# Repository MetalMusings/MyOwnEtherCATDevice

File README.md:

# MetalMusings EtherCAT device

This repository contains the EtherCAT devices I have designed, built and put in use in linuxcnc.

Everything should be here: 
- Schematics, PCB layouts, and what is needed to build the boards.
- Software tools to create an ESI-file and program the ESC eeprom. 
- Software tools to create the application running on a STM32F407VG.
- A big learning curve is hidden in here as well

I have (so far) used two different ESC ICs: LAN9252 and Ax58100. 
Both work, I can't really see a difference. 
The Ax58100 has a leg spacing of 0.4 mm, 0.5 mm for the LAN9252, if that matters.
On paper the Ax58100 has more builtin functionality like stepper motor drivers,
but the documentation is lacking. Or my understanding of the documentation is lacking.
The Ax58100 supposedly has more efficient access to registers and data.
The indirection scheme is the main objection to using LAN9252, I have read.
The LAN9252 is the true and tested IC of the two. If you don't know, go for the LAN9252.

The EtherCAT cards, which I call EaserCAT cards, use an EtherCAT chip and a normal MCU.
I have used the STM32F407VGT6. The EaserCAT chip does the network talk and other 
EtherCAT things. The STM32 does the application things, like reading and setting pins high or low,
reading encoder inputs, generate stepper motor pulses and other interesting applications one can think of.
There is a narrow interface between the two: SPI and a couple of lines for synchronization.
Any decent MCU can do that, it doesn't have to be a STM32F407VGT6. I have tested with a esp32 with success.
Feel free to experiment with other processors.

I learned most of what I know about EtherCAT through a number of Youtube videos I made.
There are accompanying git branches. For example, for video 8 you can check out the
Video8 branch to get the software tree in the state at the video.
More info on the videos, which are now more of historical interest, but also a bit of learning by following [this link](Videos.md)

And of course, this work builds on the work of many others. This would not be possible without their work. 
I'm just reusing what they did and maybe expanding on it.

Here is the start of [building instructions](Build.md)

## EaserCAT 2000 - a testbench for ESC+MCU, SOES, stepper generator, linuxcnc

This was the first card that got used in Linuxcnc. Follow [link here](Cards/EaserCAT-2000/)
I think I got it working pretty well in the end. There was, and still is, an issue with
synchronization between the linuxcnc servo-loop and the ESC DC loop.
I don't remember the status of it anymore, it was some time ago I worked with it.
The main thing was that it lacked optocouplers and isolation for the external signals.

## EaserCAT 3000 - All in one board with Ax58100

This card is an evolution of the EaserCAT 2000 and was intended to be used in my plasma cutter.
It features four stepper driver outputs, input for a THCAD arc voltage card, an encoder, 
an analog output (for spindle +- 10V), eight digital inputs, four digital outputs, 
plus some 12 I/O for any possible extension. The IOs are isolated from the MCU.

However, I couldn't get this card to work, almost at all. The Ax58100 didn't even load the eeprom. 
Struggling with the documentation for the Ax58100, which formed my negative opinion about that,
I gave up and let it sit for over half a year. It was first when someone came and asked 
questions around it I had another look. I built a new board, and it all started to work.
At time of writing it all seems to work.

The latest vesion of the firmware has all parameters for step generators as PDOs.

[Link here](Cards/EaserCAT-3000-Digital-Stepper-Analog-Encoder-Frequency/)

## EaserCAT 4000 - THCAD reader

Faced with the problems with the EaserCAT 3000 board, and still wanting to use EtherCAT 
in my upcoming plasma cutter, I made this board whos single purpose is to read 
the PWM frequency from Mesa's THCAD board.\
The THCAD board reads the voltage between 
the plasma torch and the workpiece which is around 100V. Highly isolated, and with 
a voltage to frequency converter it delivers a differential pwm signal. 
The frequency of this signal can be related to the voltage.\
That's what is needed for linuxcnc torch height control.

In the tests on the bench this can read at least up to 200 kHz, but its's better to be below 100 kHz.
The THCAD has a frequency divider one can set to make the frequency range nicely match this.
It seems to work fine so far. 
Implementation is with interrupts. \
A better option would have been to use TIM2's PWM_INPUT function, which can work with several MHz frequency. 
I tried the PWM_INPUT method a lot but couldn't get it to work. The current method still works, though.
If time and interests are in phase with the moon, I might look at PWM_INPUT again.

This board is now relegated to history, replaced by the EaserCAT-6000.

[Link here](Cards/EaserCAT-4000-THCAD-Reader/)

## EaserCAT 5000 - Digital IO without MCU

A card just doing Digital Input and Digital Output. The intentions were to read 
limit switches and some other switches around the plasma torch. And to switch on the plasma torch.
It's a single LAN9252, configured for local IO. Optocouplers are attached to IO pins for isolation.
It has been tested on the bench, it works with TwinCAT.

HOWEVER, it doesn't work, and will not work, with linuxcnc. As I've learned,
the IgH EtherCAT master needs a CoE client (CANopen over EtherCAT).
The LAN9252 in DIO mode is only an EtherCAT client and can't be turned
into a CoE client. And the IgH EtherCAT application interface for real-time
communication can not be downgraded to work with a pure EtherCAT client,
it requires a CoE client.

To add CoE functionality means to add number of objects at certain positions
in the client and that can not be done to the LAN9252. It is what it is.
In a setup with LAN9252 with MCU, those objects are created in the firmware,
so there it works.

This board is now relegated to history, replaced by the EaserCAT-6000.

## EaserCAT 6000 - Digital IO and frequency input

Finally, a card that's actually used in a real system. This card is used in my plasma cutter. 
It has 12 digital inputs, 4 digital outputs and a frequency counter to get
the input from Mesa's THCAD (reader of voltage between plasma nozzle and workpiece).\
All digital IOs are opto-isolated and the frequency input uses a RS-485 receiver.

In the plasma cutter, it does the job. There are three ECT60 stepper motor drivers.
And the EaserCAT-6000 card. It handles limit switches for X, Y and Z, floating switch,
break-away switch, and plasma Arc OK signal. There is room for e-stop and other switches.\
The plasma torch is switched on using one of the digital outputs.\
THCAD is an older model with full voltage input. Frequency divider is set to 1/32.

This board replaces EaserCAT-4000 and EaserCAT-5000. 

[Link here](Cards/EaserCAT-6000-THCAD-reader+Digital-IO/)

A few weeks later and I've used this card in the plasma cutter for quite a bit of cutting and it hasn't missed a beat. Works so well. THC follows the sheet surface up and down. Awesome.

## EaserCAT Torch Height Control - EaserCAT 7000 with THTIC and THTIC2

Actually something useful again - not one, but two, plasma torch voltage readers.
They replace the THCAD board and comes with the entire chain from voltage reading to the introduction of a calibrated voltage to linuxcnc for use in QtPlasmaC. 

Let's start with the plasma cutter. There is either a THTIC or THTIC2 mini-board, which reads the plasma torch voltage, and through a voltage divider lowers it to about 2 Volts during cutting. This voltage is converted by an analog to digital converter and feeds the digitized voltage to the EaserCAT 7000 board via an I2C bus (cable). The EaserCAT 7000 board makes the voltage available both as the raw read voltage for further scaling, or as a calibrated voltage using entered calibration constants.

The plasma torch voltage is DCEN - DC Electrode Negative. The workpiece ground is often connected to ground/earth.
With ground as the reference voltage, the plasma torch voltage ranges between 0 V and -200 V.
An inverting operational amplifier switches the polarity for the ADC. The ground planes on the circuit board are connected to the workpiece ground.

An important feature of THCTIC and THCTIC2 is that the plasma voltage side is isolated from the linuxcnc signal side. The isolation level is better than 1.5 kV. This is achieved by an I2C isolator and an isolated DC-DC converter. The difference between the two cards is the choice of ADC. THTIC uses MCP3221 and THTIC2 uses ADS1014. Both are 12-bit analog to digital converters, ADS1014 is perhaps an 11-bit, both with sampling rates around 3 kHz. A newly measured voltage value can be obtained every 1 ms. Of course you only choose one of the two. Since it seemed pretty easy when I did it, I made two different ones. Always good to have options.

The boards are relatively small, 42x30 mm. Voltage 5V in, current less than 10 mA. I2C Data and clock. 

### THTIC

### THTIC2

### EaserCAT-7000 Digital IO and I2C voltage reader

EaserCAT-7000 is an EaserCAT-6000 board where the THCAD frequency input has been replaced by the I2C bus.
There are twelve digital inputs and four digital outputs.

Currently the EaserCAT-7000 can handle two I2C voltage readers, on different I2C addresses.\
Configuration of the connected I2C devices is done by setting the voltage reader type in SDOs 0x2000:1 and 0x2001:1 for device 1 and 2. The I2C device type is set to 0 by default. A zero means no I2C ADC. Entering a 1 in 0x2000:0 selects the MCP3221, and a 2 in 0x2000:0 selects the ADS1014.\
The I2C address for the ADC is written into SDOs 0x2000:2 and 0x2001:2. The address for the MCP3221 is selected when it is purchased - there are 8 different models each with a different I2C address 0x48-0x4f. The THTIC2 board has the address fixed at 0x48; can be modified during pcb assembly to 0x49 quite easily - check datasheet. Short version is to cut Addr-Gnd and add Addr-Vcc.

Pay attention to the polarity when connecting the plasma voltage leads the THTIC and THTIC2. Varc+ must have higher voltage potential the Varc- (as one would expect). The voltage divisor may need to be adjusted, there is now one 100 kOhm resistor and a 2.2 kOhm resistor, which brings down 100 V to around 2 V. Adjust as needed. For high voltage, pay attention to the max allowed voltage of the resistor. The ADC likes to have around 2-3 Volts when cutting.

The experience with these cards has been very good. I used the THTIC a lot, cutting for at least an hour of cutting time, with THC enabled and active. A status variable shows that it has been working the whole time, no stops or resets. After that I switched to the THTIC2 card and have been using that since. Works really well.

## THCLIP Enable ohmic sensing with the IPTM-60 torch

This is for the torches known as IPT-60 PT-60 S45 IPTM-60 IPTM-80 and many more that have blowback start with the torch tip exposed and normally shortened to the torch electrode. Normally this torch can't use ohmic sensing since all parts are connected to ground. At least on my machine, a Herocut 8000, the blowback start cable from the torch can be cut during sensing. This enables ohmic sensing and it continues to operate in other situations.

I tried at first to use the normal Arc voltage reader to detect any contact between the torch and the work piece during probing. However, that was not reliable - it seems there is electronics involved with the arc voltage. Don't want to know details. 

I put a second voltage reader THTIC2 close to the THCLIP and measure the 24V applied after the relay. Monitoring this voltage turns out to be reliable and makes the ohmic sensing work really well.

I have made an adaptation to the EaserCAT 7000 to handle the contact. The relay has a short, some 10 msecs, setup time. The read voltage must therefor first go above the voltage limit before it starts to scan for the voltage to go below the voltage limit which indicates contact.

The Trafimet torch hose connectors are called FY0022 and FY0023. The relay is a 24V 40A standard car relay. Check out the Kicad schematics for the other parts.

Leads 1 and 4 are the blowback arc start ground leads in my torch. They get cut by the relay during ohmic sensing. Voltage is measured on connector J3, between pin 1 and pin 2.

## License

Don't violate the original licenses. No warranties. Use it any way you like.\
Remember: It is a hobby project, not a product.

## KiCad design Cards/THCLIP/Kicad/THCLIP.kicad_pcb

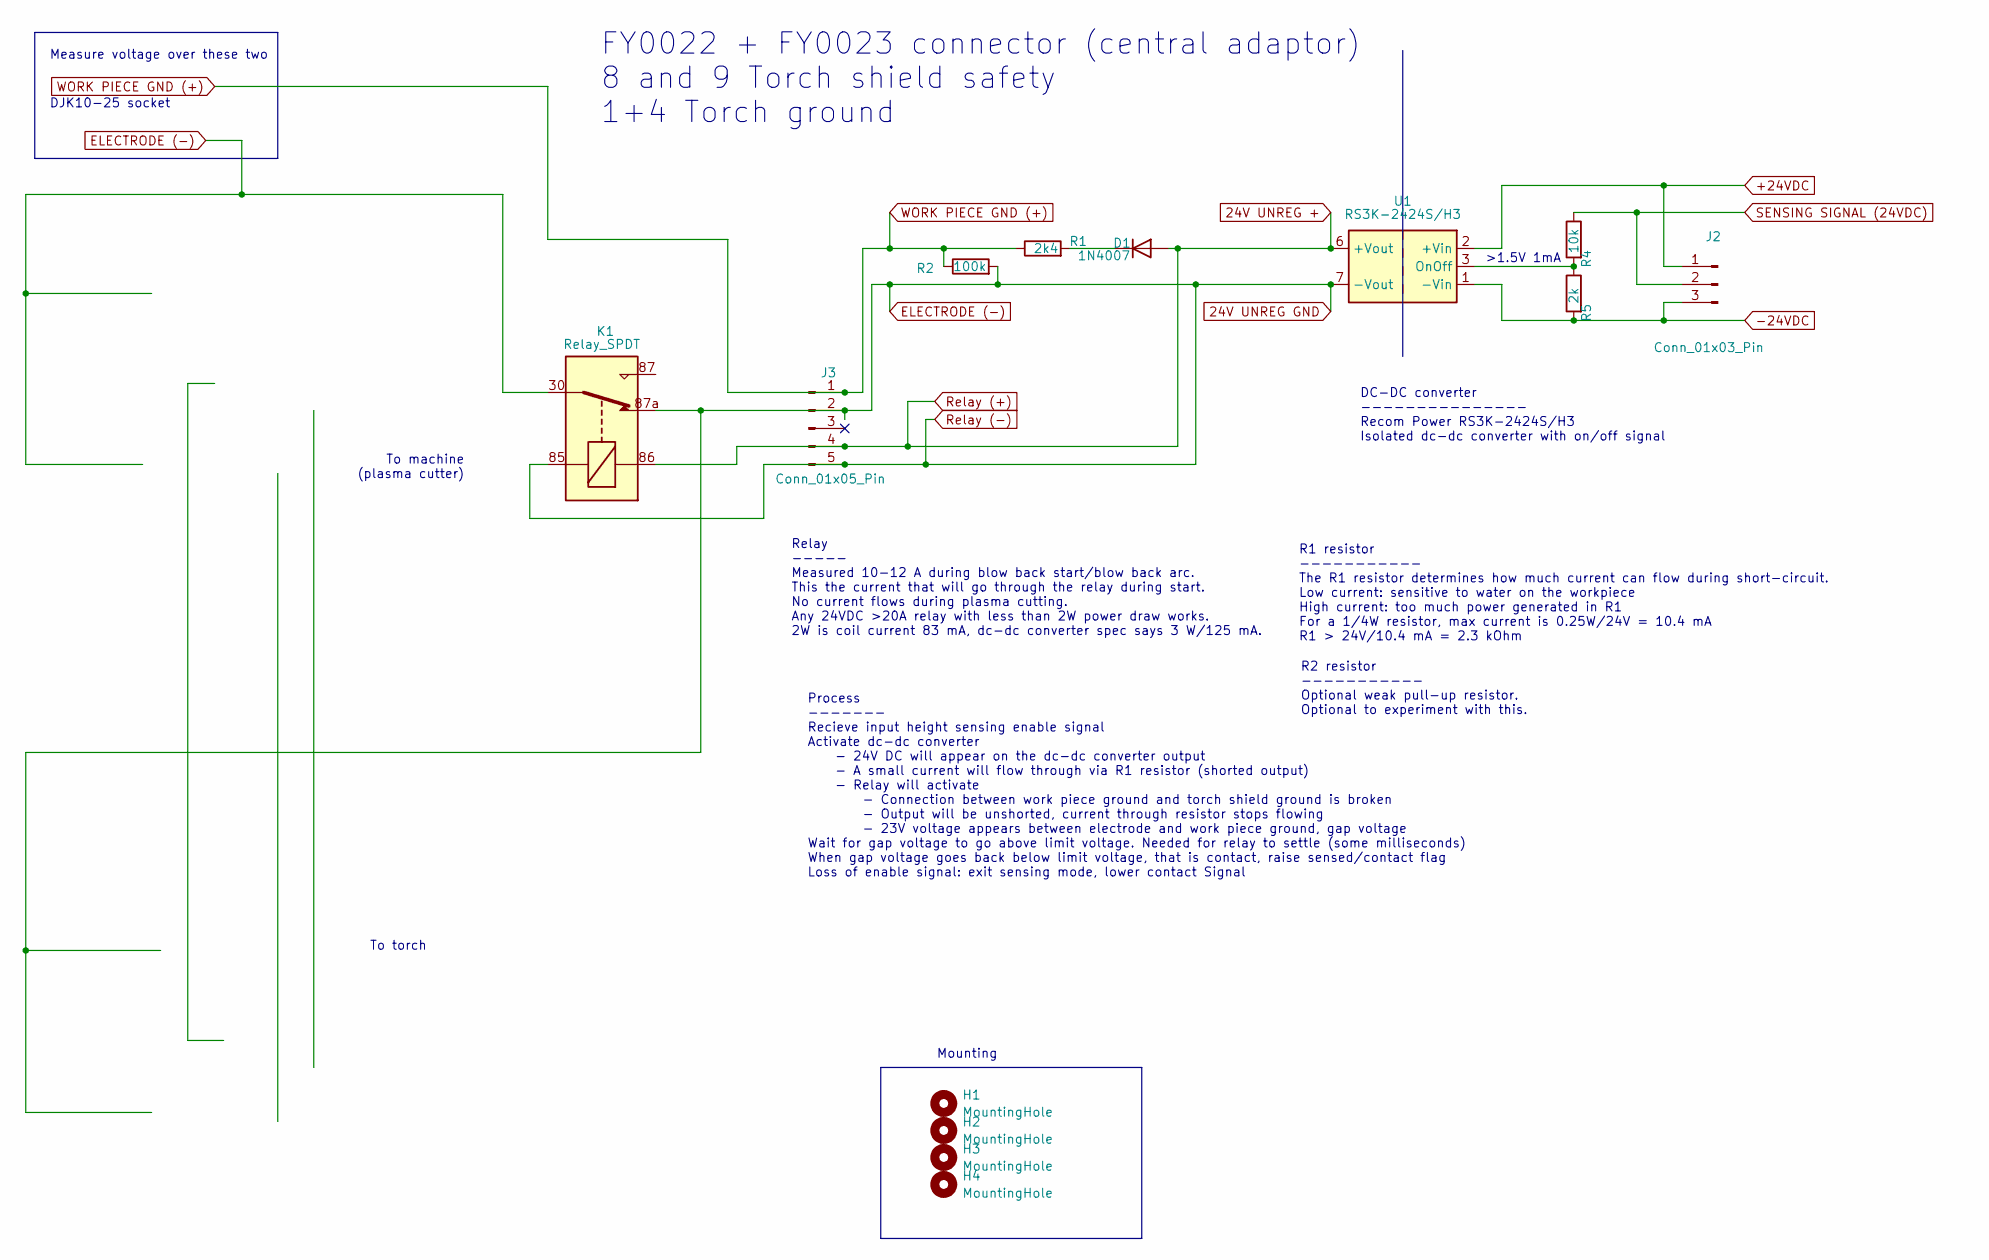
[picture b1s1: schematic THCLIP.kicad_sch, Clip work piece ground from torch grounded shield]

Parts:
D1: 1N4007; D_DO-41_SOD81_P10.16mm_Horizontal
H1, H2, H3, H4: MountingHole; MountingHole_3.2mm_M3
J2: Conn_01x03_Pin; PhoenixContact_MCV_1,5_3-G-3.5_1x03_P3.50mm_Vertical
J3: Conn_01x05_Pin; PhoenixContact_MCV_1,5_5-G-3.5_1x05_P3.50mm_Vertical
K1: Relay_SPDT
R1: 2k4; R_Axial_DIN0207_L6.3mm_D2.5mm_P10.16mm_Horizontal
R2: 100k; R_Axial_DIN0207_L6.3mm_D2.5mm_P10.16mm_Horizontal
R4: 10k; R_0805_2012Metric_Pad1.20x1.40mm_HandSolder
R5: 2k; R_0805_2012Metric_Pad1.20x1.40mm_HandSolder
U1: RS3K-2424S/H3; Converter_DCDC_TRACO_TEC3-24xxUI_THT

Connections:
24V UNREG +: D1.2 (A), J3.4, K1.86, U1.6 (+Vout)
24V UNREG GND: J3.2, J3.5, K1.30, K1.85, K1.87a, R2.2, U1.7 (-Vout)
+24VDC: J2.1, U1.2 (+Vin)
-24VDC: J2.3, R5.2, U1.1 (-Vin)
unnamed: D1.1 (K), R1.2
unnamed: R4.2, R5.1, U1.3 (OnOff)
SENSING SIGNAL (24VDC): J2.2, R4.1
WORK PIECE GND (+): J3.1, R1.1, R2.1

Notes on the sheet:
DJK10-25 socket
Process ------- Recieve input height sensing enable signal Activate dc-dc converter - 24V DC will appear on the dc-dc converter output - A small current will flow through via R1 resistor (shorted output) - Relay will activate - Connection between work piece ground and torch shield ground is broken 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
>1.5V 1mA
To torch
Mounting
To machine (plasma cutter)
FY0022 + FY0023 connector (central adaptor) 8 and 9 Torch shield safety 1+4 Torch ground
Measure voltage over these two
R1 resistor ----------- The R1 resistor determines how much current can flow during short-circuit. Low current: sensitive to water on the workpiece High current: too much power generated in R1 For a 1/4W resistor, max current is 0.25W/24V = 10.4 mA R1 > 24V/10.4 mA = 2.3 kOhm
DC-DC converter --------------- Recom Power RS3K-2424S/H3 Isolated dc-dc converter with on/off signal
R2 resistor ----------- Optional weak pull-up resistor. Optional to experiment with this.
Relay ----- Measured 10-12 A during blow back start/blow back arc. This the current that will go through the relay during start. No current flows during plasma cutting. Any 24VDC >20A relay with less than 2W power draw works. 2W is coil current 83 mA, dc-dc converter spec says 3 W/125 mA.

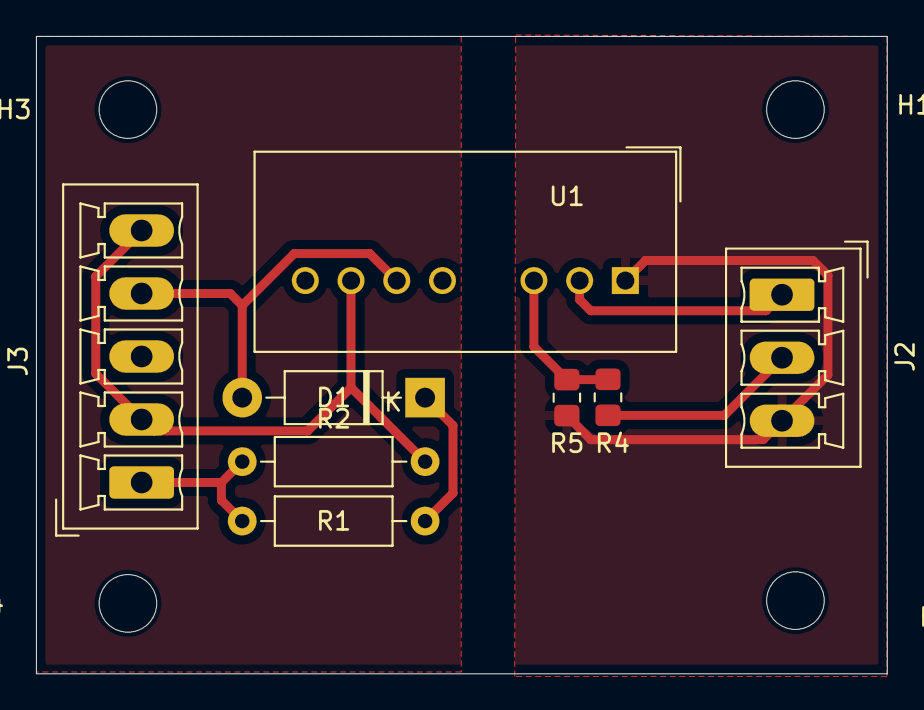
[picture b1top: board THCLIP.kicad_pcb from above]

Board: 2 copper layers, 47.3 x 35.4 mm, 12 parts (0 on the bottom side), 8 nets.

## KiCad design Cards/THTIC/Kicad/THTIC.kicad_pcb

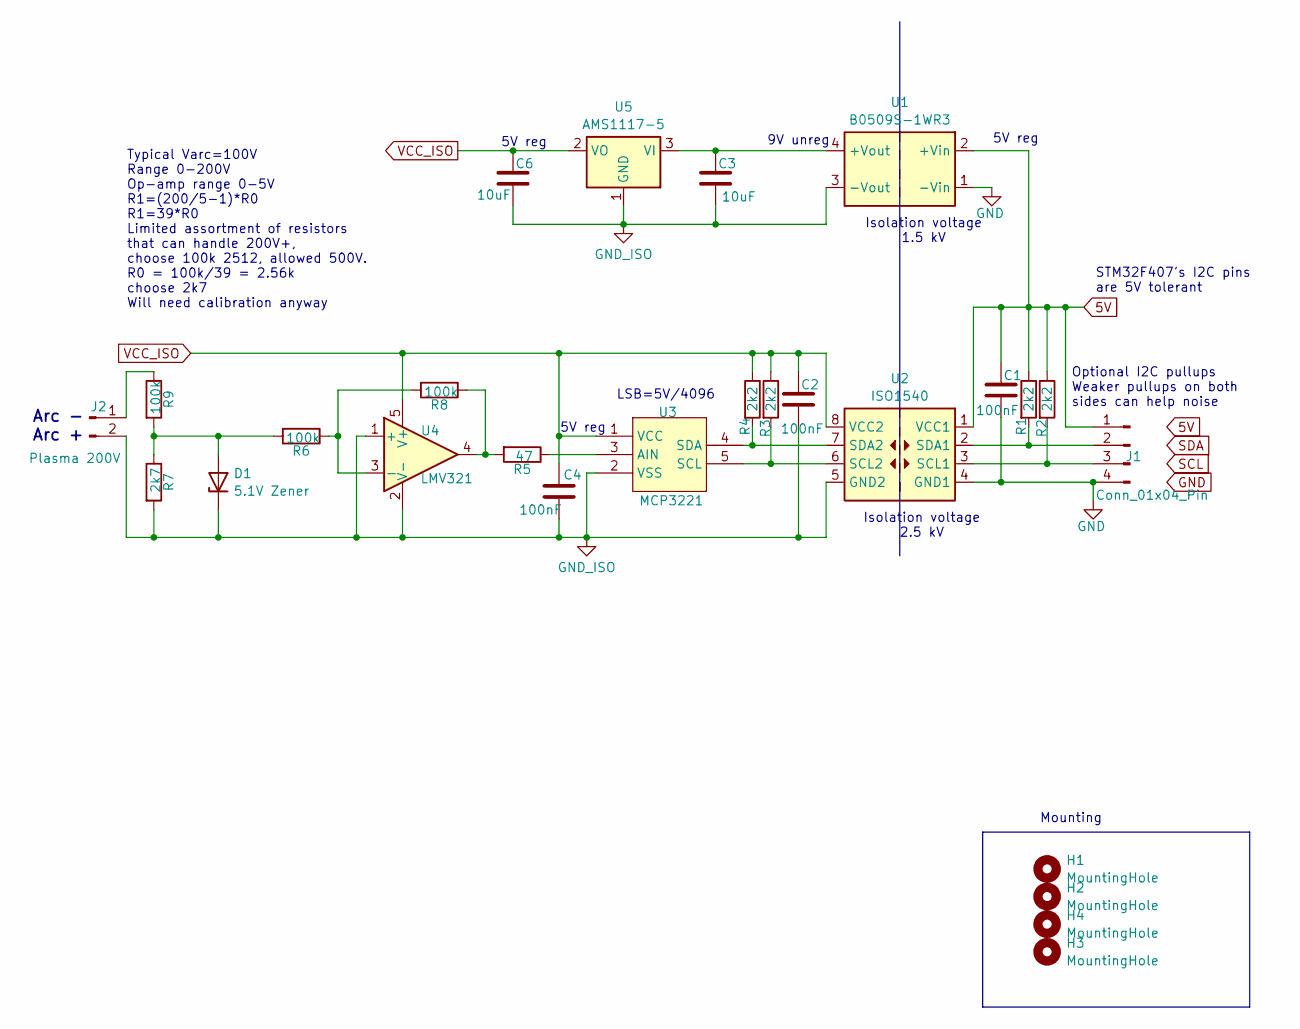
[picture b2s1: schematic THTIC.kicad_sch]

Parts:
C1, C2, C4: 100nF; C_0805_2012Metric
C3, C6: 10uF; C_0805_2012Metric
D1: 5.1V Zener; D_SOD-323_HandSoldering
H1, H2, H3, H4: MountingHole; MountingHole_3.2mm_M3
J1: Conn_01x04_Pin; PhoenixContact_MCV_1,5_4-G-3.5_1x04_P3.50mm_Vertical
J2: Plasma 200V; PhoenixContact_MCV_1,5_2-G-3.5_1x02_P3.50mm_Vertical
R1, R2, R3, R4: 2k2; R_0805_2012Metric
R5: 47; R_0805_2012Metric
R6, R8: 100k; R_0805_2012Metric
R7: 2k7; R_0805_2012Metric
R9: 100k; R_2512_6332Metric
U1: B0509S-1WR3; Converter_DCDC_TRACO_TEA1-xxxx_THT
U2: ISO1540; SOIC-8_3.9x4.9mm_P1.27mm
U3: MCP3221; SOT-23-5
U4: LMV321; SOT-23-5
U5: AMS1117-5; SOT-223-3_TabPin2

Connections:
5V: C1.1, J1.1, R1.1, R2.1, U1.2 (+Vin), U2.1 (VCC1)
GND: C1.2, J1.4, U1.1 (-Vin), U2.4 (GND1)
GND_ISO: C2.2, C3.2, C4.2, C6.2, D1.1 (K), J2.2, R7.2, U1.3 (-Vout), U2.5 (GND2), U3.2 (VSS), U4.1 (+), U4.2 (V-), U5.1 (GND); also elsewhere on the board
unnamed: D1.2 (A), R6.2, R7.1, R9.2
unnamed: J1.2, R1.2, U2.2 (SDA1)
unnamed: J1.3, R2.2, U2.3 (SCL1)
unnamed: J2.1, R9.1
unnamed: R5.2, R8.1, U4.4
unnamed: C3.1, U1.4 (+Vout), U5.3 (VI)
unnamed: R3.2, U2.6 (SCL2), U3.5 (SCL)
unnamed: R4.2, U2.7 (SDA2), U3.4 (SDA)
unnamed: R5.1, U3.3 (AIN)
unnamed: R6.1, R8.2, U4.3 (-)
VCC_ISO: C2.1, C4.1, C6.1, R3.1, R4.1, U2.8 (VCC2), U3.1 (VCC), U4.5 (V+), U5.2 (VO); also elsewhere on the board

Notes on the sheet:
Mounting
5V reg
Isolation voltage 2.5 kV
STM32F407's I2C pins are 5V tolerant
9V unreg
LSB=5V/4096
Optional I2C pullups Weaker pullups on both sides can help noise
Isolation voltage 1.5 kV
Typical Varc=100V Range 0-200V Op-amp range 0-5V R1=(200/5-1)*R0 R1=39*R0 Limited assortment of resistors that can handle 200V+, choose 100k 2512, allowed 500V. R0 = 100k/39 = 2.56k choose 2k7 Will need calibration anyway
Arc - Arc +

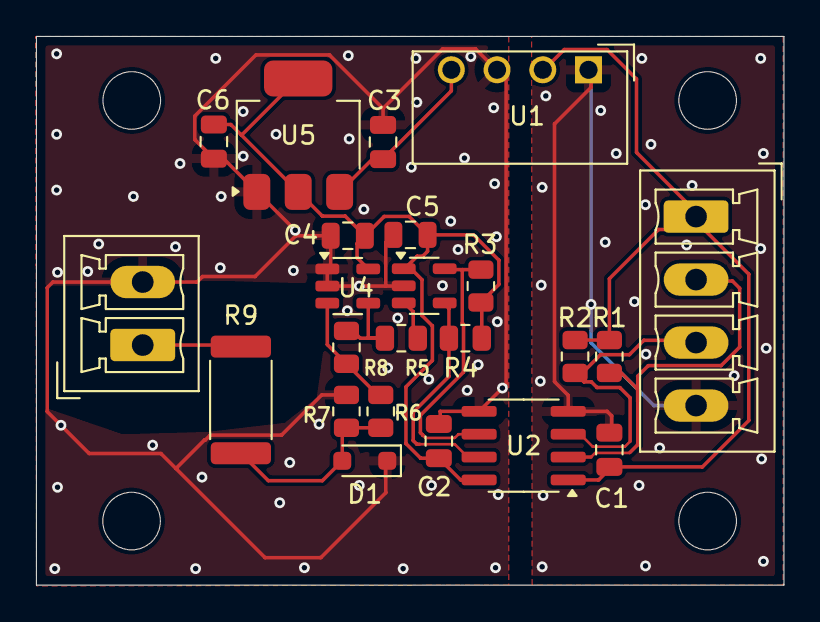
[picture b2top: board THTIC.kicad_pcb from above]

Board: 2 copper layers, 41.5 x 30.5 mm, 27 parts (0 on the bottom side), 14 nets.

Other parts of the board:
C5: 100nF; C_0805_2012Metric

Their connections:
GND_ISO: C5.2; also elsewhere on the board
VCC_ISO: C5.1; also elsewhere on the board

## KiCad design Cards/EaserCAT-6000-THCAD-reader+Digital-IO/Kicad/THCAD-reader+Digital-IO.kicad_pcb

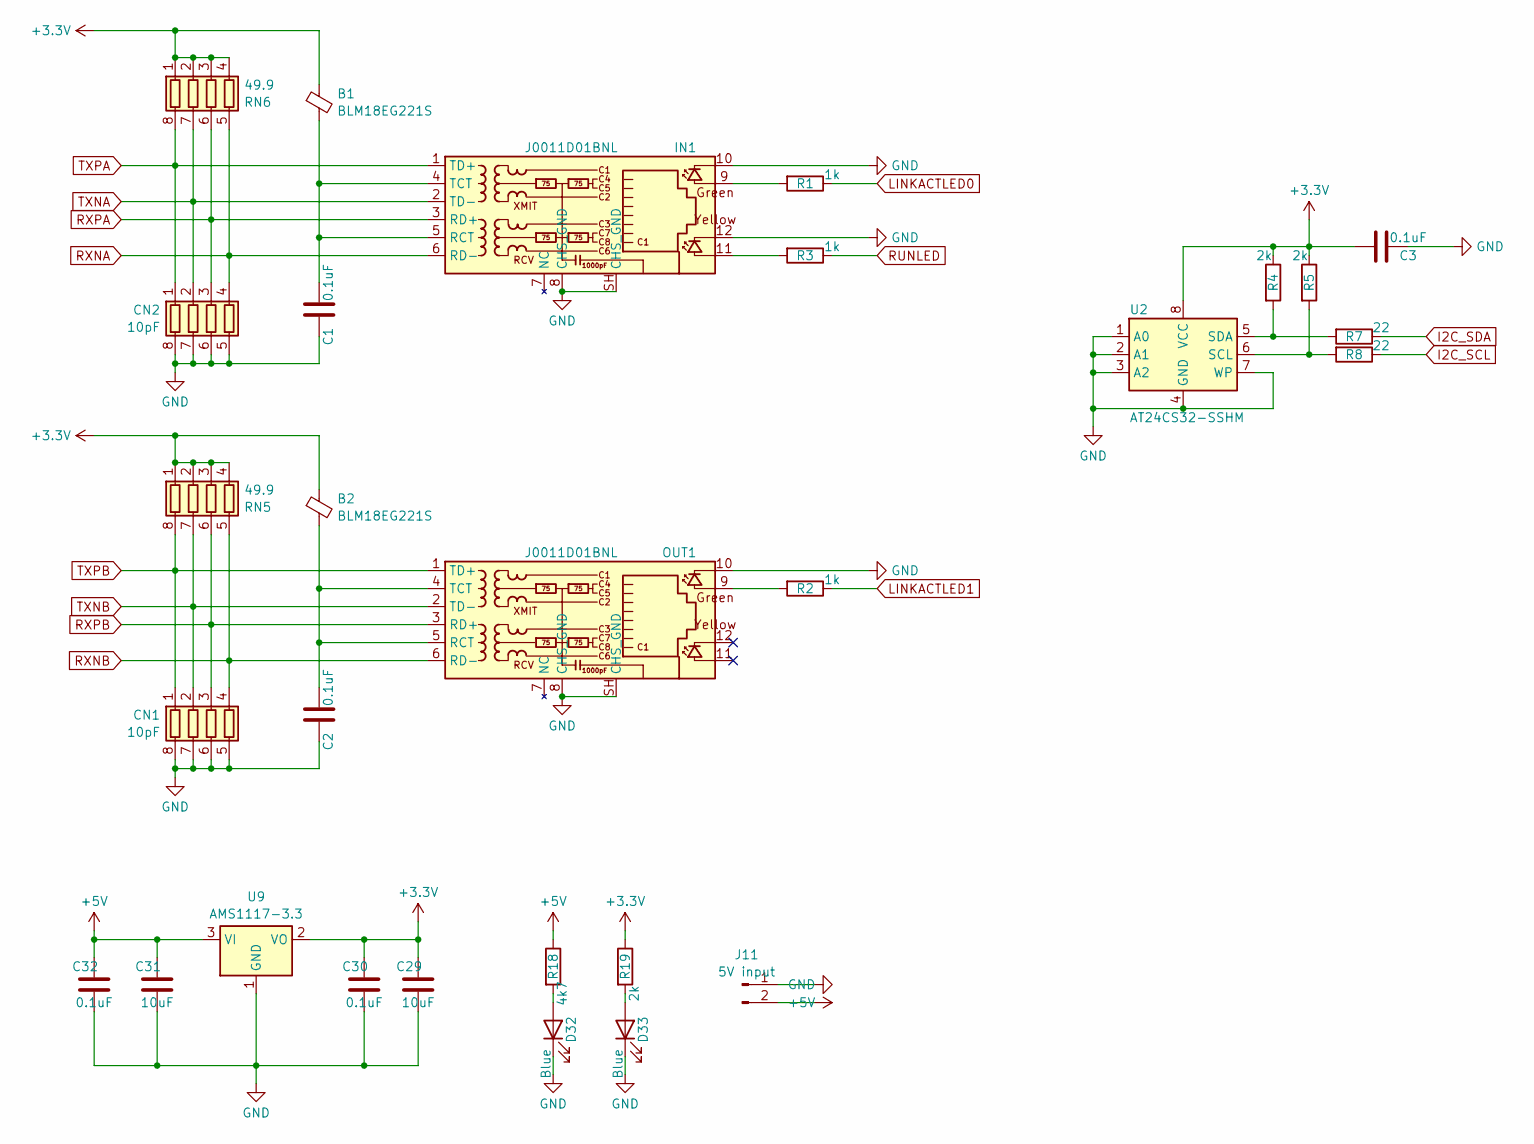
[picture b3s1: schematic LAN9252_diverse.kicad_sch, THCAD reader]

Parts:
B1, B2: BLM18EG221S; C_0805_2012Metric
C1, C2, C3, C30, C32: 0.1uF; C_0603_1608Metric
C29, C31: 10uF; C_0603_1608Metric
CN1, CN2: 10pF; R_Array_Convex_4x0603
D32, D33: Blue; LED_0603_1608Metric
IN1: J0011D01BNL; PulseJack JB0011D01BNL
J11: 5V input; PhoenixContact_MCV_1,5_2-G-3.5_1x02_P3.50mm_Vertical
OUT1: J0011D01BNL; PulseJack JB0011D01BNL
R1, R2, R3: 1k; R_0603_1608Metric
R4, R5, R19: 2k; R_0603_1608Metric
R7, R8: 22; R_0603_1608Metric
R18: 4k7; R_0603_1608Metric
RN5, RN6: 49.9; R_Array_Convex_4x0603
U2: AT24CS32-SSHM; SOIC-8_3.9x4.9mm_P1.27mm
U9: AMS1117-3.3; SOT-223-3_TabPin2

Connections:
+3.3V: B1.1, B2.1, C3.2, C29.1, C30.1, R4.1, R5.1, R19.1, RN5.1 (R1.1), RN5.2 (R2.1), RN5.3 (R3.1), RN5.4 (R4.1), RN6.1 (R1.1), RN6.2 (R2.1), RN6.3 (R3.1), RN6.4 (R4.1), U2.8 (VCC), U9.2 (VO); also elsewhere on the board
+5V: C31.1, C32.1, J11.2, R18.1, U9.3 (VI); also elsewhere on the board
GND: C1.1, C2.1, C3.1, C29.2, C30.2, C31.2, C32.2, CN1.5 (R4.2), CN1.6 (R3.2), CN1.7 (R2.2), CN1.8 (R1.2), CN2.5 (R4.2), CN2.6 (R3.2), CN2.7 (R2.2), CN2.8 (R1.2), D32.1 (K), D33.1 (K), IN1.8 (CHS_GND), IN1.10, IN1.12, IN1.SH (CHS_GND), J11.1, OUT1.8 (CHS_GND), OUT1.10, OUT1.SH (CHS_GND), U2.1 (A0), U2.2 (A1), U2.3 (A2), U2.4 (GND), U2.7 (WP), U9.1 (GND); also elsewhere on the board
I2C_SCL: R8.1; also elsewhere on the board
I2C_SDA: R7.1; also elsewhere on the board
LINKACTLED0: R1.1; also elsewhere on the board
LINKACTLED1: R2.1; also elsewhere on the board
unnamed: D32.2 (A), R18.2
unnamed: D33.2 (A), R19.2
unnamed: IN1.9, R1.2
unnamed: IN1.11, R3.2
unnamed: B1.2, C1.2, IN1.4 (TCT), IN1.5 (RCT)
unnamed: OUT1.9, R2.2
unnamed: B2.2, C2.2, OUT1.4 (TCT), OUT1.5 (RCT)
unnamed: R5.2, R8.2, U2.6 (SCL)
unnamed: R4.2, R7.2, U2.5 (SDA)
RUNLED: R3.1; also elsewhere on the board
RXNA: CN2.4 (R4.1), IN1.6 (RD-), RN6.5 (R4.2); also elsewhere on the board
RXNB: CN1.4 (R4.1), OUT1.6 (RD-), RN5.5 (R4.2); also elsewhere on the board
RXPA: CN2.3 (R3.1), IN1.3 (RD+), RN6.6 (R3.2); also elsewhere on the board
RXPB: CN1.3 (R3.1), OUT1.3 (RD+), RN5.6 (R3.2); also elsewhere on the board
TXNA: CN2.2 (R2.1), IN1.2 (TD-), RN6.7 (R2.2); also elsewhere on the board
TXNB: CN1.2 (R2.1), OUT1.2 (TD-), RN5.7 (R2.2); also elsewhere on the board
TXPA: CN2.1 (R1.1), IN1.1 (TD+), RN6.8 (R1.2); also elsewhere on the board
TXPB: CN1.1 (R1.1), OUT1.1 (TD+), RN5.8 (R1.2); also elsewhere on the board

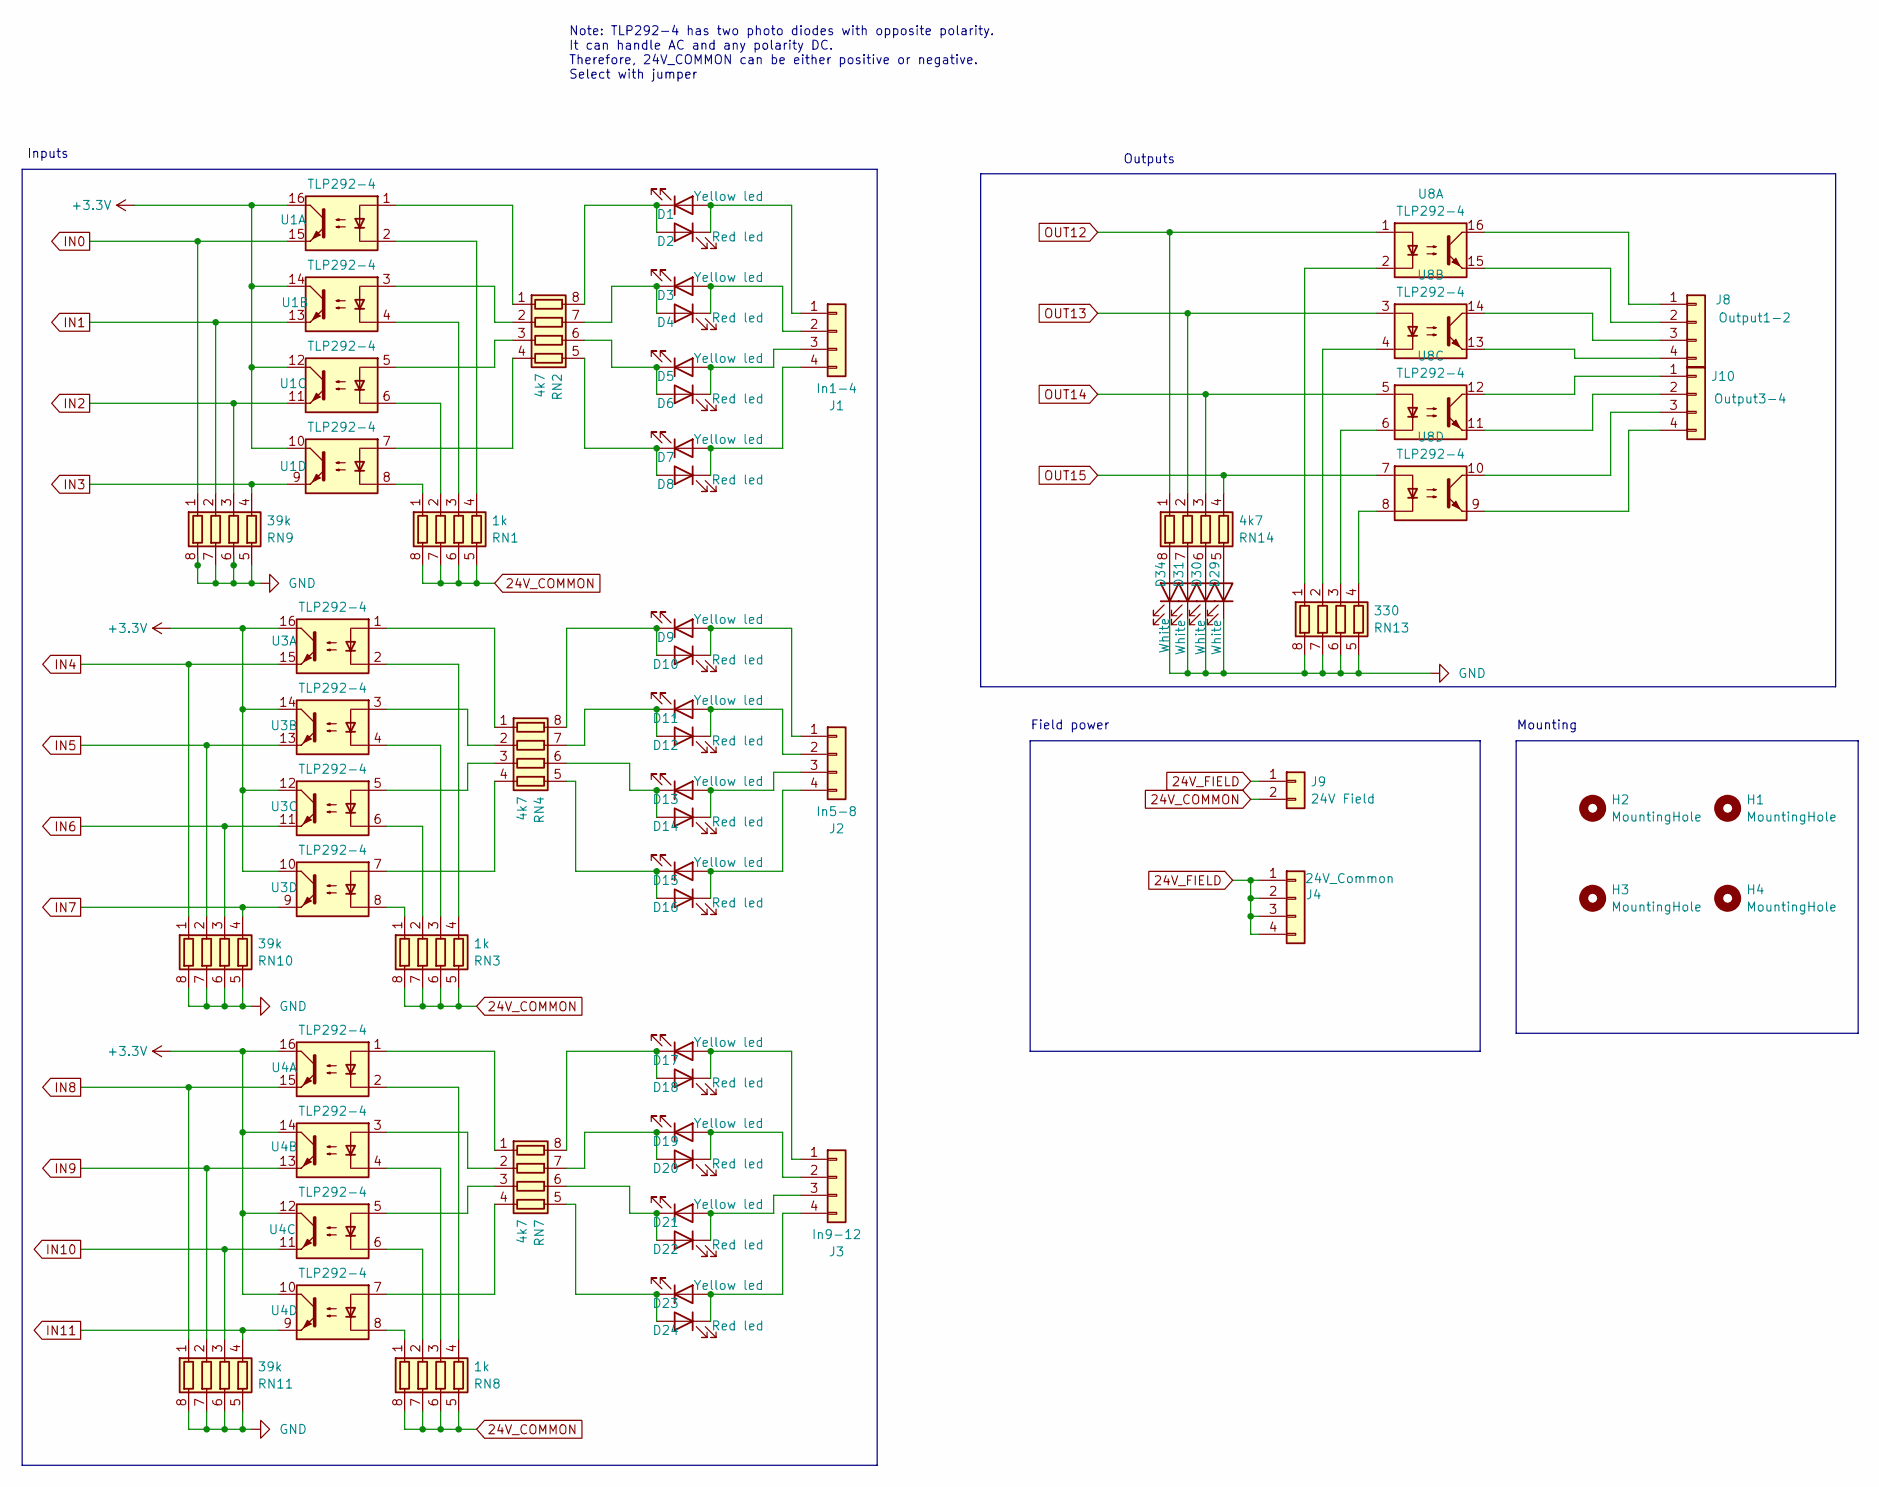
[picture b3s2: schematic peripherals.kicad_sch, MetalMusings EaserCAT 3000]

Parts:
D1, D3, D5, D7, D9, D11, D13, D15, D17, D19, D21, D23: Yellow led; LED_0603_1608Metric
D2, D4, D6, D8, D10, D12, D14, D16, D18, D20, D22, D24: Red led; LED_0603_1608Metric
D29, D30, D31, D34: White; LED_0603_1608Metric
H1, H2, H3, H4: MountingHole; MountingHole_3.2mm_M3_ISO14580
J1: In1-4; PhoenixContact_MCV_1,5_4-G-3.5_1x04_P3.50mm_Vertical
J2: In5-8; PhoenixContact_MCV_1,5_4-G-3.5_1x04_P3.50mm_Vertical
J3: In9-12; PhoenixContact_MCV_1,5_4-G-3.5_1x04_P3.50mm_Vertical
J4: 24V_Common; PhoenixContact_MCV_1,5_4-G-3.5_1x04_P3.50mm_Vertical
J8: Output1-2; PhoenixContact_MCV_1,5_4-G-3.5_1x04_P3.50mm_Vertical
J9: 24V Field; PhoenixContact_MCV_1,5_2-G-3.5_1x02_P3.50mm_Vertical
J10: Output3-4; PhoenixContact_MCV_1,5_4-G-3.5_1x04_P3.50mm_Vertical
RN1, RN3, RN8: 1k; R_Array_Convex_4x0603
RN2, RN4, RN7, RN14: 4k7; R_Array_Convex_4x0603
RN9, RN10, RN11: 39k; R_Array_Convex_4x0603
RN13: 330; R_Array_Convex_4x0603
U1, U3, U4, U8: TLP292-4; SOIC-16_4.55x10.3mm_P1.27mm

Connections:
24V_COMMON: J9.2, RN1.5 (R4.2), RN1.6 (R3.2), RN1.7 (R2.2), RN1.8 (R1.2), RN3.5 (R4.2), RN3.6 (R3.2), RN3.7 (R2.2), RN3.8 (R1.2), RN8.5 (R4.2), RN8.6 (R3.2), RN8.7 (R2.2), RN8.8 (R1.2)
24V_FIELD: J4.1, J4.2, J4.3, J4.4, J9.1
+3.3V: U1.10, U1.12, U1.14, U1.16, U3.10, U3.12, U3.14, U3.16, U4.10, U4.12, U4.14, U4.16; also elsewhere on the board
GND: D29.1 (K), D30.1 (K), D31.1 (K), D34.1 (K), RN9.5 (R4.2), RN9.6 (R3.2), RN9.7 (R2.2), RN9.8 (R1.2), RN10.5 (R4.2), RN10.6 (R3.2), RN10.7 (R2.2), RN10.8 (R1.2), RN11.5 (R4.2), RN11.6 (R3.2), RN11.7 (R2.2), RN11.8 (R1.2), RN13.5 (R4.2), RN13.6 (R3.2), RN13.7 (R2.2), RN13.8 (R1.2); also elsewhere on the board
IN0: RN9.1 (R1.1), U1.15; also elsewhere on the board
IN1: RN9.2 (R2.1), U1.13; also elsewhere on the board
IN2: RN9.3 (R3.1), U1.11; also elsewhere on the board
IN3: RN9.4 (R4.1), U1.9; also elsewhere on the board
IN4: RN10.1 (R1.1), U3.15; also elsewhere on the board
IN5: RN10.2 (R2.1), U3.13; also elsewhere on the board
IN6: RN10.3 (R3.1), U3.11; also elsewhere on the board
IN7: RN10.4 (R4.1), U3.9; also elsewhere on the board
IN8: RN11.1 (R1.1), U4.15; also elsewhere on the board
IN9: RN11.2 (R2.1), U4.13; also elsewhere on the board
IN10: RN11.3 (R3.1), U4.11; also elsewhere on the board
IN11: RN11.4 (R4.1), U4.9; also elsewhere on the board
unnamed: D1.2 (A), D2.1 (K), J1.1
unnamed: D1.1 (K), D2.2 (A), RN2.8 (R1.2)
unnamed: D3.2 (A), D4.1 (K), J1.2
unnamed: D3.1 (K), D4.2 (A), RN2.7 (R2.2)
unnamed: D5.2 (A), D6.1 (K), J1.3
unnamed: D5.1 (K), D6.2 (A), RN2.6 (R3.2)
unnamed: D7.2 (A), D8.1 (K), J1.4
unnamed: D7.1 (K), D8.2 (A), RN2.5 (R4.2)
unnamed: D9.1 (K), D10.2 (A), RN4.8 (R1.2)
unnamed: D9.2 (A), D10.1 (K), J2.1
unnamed: D11.2 (A), D12.1 (K), J2.2
unnamed: D11.1 (K), D12.2 (A), RN4.7 (R2.2)
unnamed: D13.2 (A), D14.1 (K), J2.3
unnamed: D13.1 (K), D14.2 (A), RN4.6 (R3.2)
unnamed: D15.2 (A), D16.1 (K), J2.4
unnamed: D15.1 (K), D16.2 (A), RN4.5 (R4.2)
unnamed: D17.2 (A), D18.1 (K), J3.1
unnamed: D17.1 (K), D18.2 (A), RN7.8 (R1.2)
unnamed: D19.2 (A), D20.1 (K), J3.2
unnamed: D19.1 (K), D20.2 (A), RN7.7 (R2.2)
unnamed: D21.2 (A), D22.1 (K), J3.3
unnamed: D21.1 (K), D22.2 (A), RN7.6 (R3.2)
unnamed: D23.2 (A), D24.1 (K), J3.4
unnamed: D23.1 (K), D24.2 (A), RN7.5 (R4.2)
unnamed: D29.2 (A), RN14.5 (R4.2)
unnamed: D30.2 (A), RN14.6 (R3.2)
unnamed: D31.2 (A), RN14.7 (R2.2)
unnamed: D34.2 (A), RN14.8 (R1.2)
unnamed: J8.1, U8.16
unnamed: J8.2, U8.15
unnamed: J8.3, U8.14
unnamed: J8.4, U8.13
unnamed: J10.1, U8.12
unnamed: J10.2, U8.11
unnamed: J10.3, U8.10
unnamed: J10.4, U8.9
unnamed: RN1.1 (R1.1), U1.8
unnamed: RN1.2 (R2.1), U1.6
unnamed: RN1.3 (R3.1), U1.4
unnamed: RN1.4 (R4.1), U1.2
unnamed: RN2.1 (R1.1), U1.1
unnamed: RN2.2 (R2.1), U1.3
unnamed: RN2.3 (R3.1), U1.5
unnamed: RN2.4 (R4.1), U1.7
unnamed: RN3.1 (R1.1), U3.8
unnamed: RN3.2 (R2.1), U3.6
unnamed: RN3.3 (R3.1), U3.4
unnamed: RN3.4 (R4.1), U3.2
unnamed: RN4.1 (R1.1), U3.1
unnamed: RN4.2 (R2.1), U3.3
unnamed: RN4.3 (R3.1), U3.5
unnamed: RN4.4 (R4.1), U3.7
unnamed: RN7.1 (R1.1), U4.1
unnamed: RN7.2 (R2.1), U4.3
unnamed: RN7.3 (R3.1), U4.5
unnamed: RN7.4 (R4.1), U4.7
unnamed: RN8.1 (R1.1), U4.8
unnamed: RN8.2 (R2.1), U4.6
unnamed: RN8.3 (R3.1), U4.4
unnamed: RN8.4 (R4.1), U4.2
unnamed: RN13.1 (R1.1), U8.2
unnamed: RN13.2 (R2.1), U8.4
unnamed: RN13.3 (R3.1), U8.6
unnamed: RN13.4 (R4.1), U8.8
OUT12: RN14.1 (R1.1), U8.1; also elsewhere on the board
OUT13: RN14.2 (R2.1), U8.3; also elsewhere on the board
OUT14: RN14.3 (R3.1), U8.5; also elsewhere on the board
OUT15: RN14.4 (R4.1), U8.7; also elsewhere on the board

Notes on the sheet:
Inputs
Mounting
Outputs
Field power
Note: TLP292-4 has two photo diodes with opposite polarity. It can handle AC and any polarity DC. Therefore, 24V_COMMON can be either positive or negative. Select with jumper
